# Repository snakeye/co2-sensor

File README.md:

# Carbon Dioxide Sensor MH-Z19b - ESP8266 Prototype

This project utilizes the MH-Z19b carbon dioxide sensor module, which provides a simple and cost-effective way to measure CO2 concentration via UART interface. The sensor measures concentrations in the range of 0-5000ppm, making it suitable for various environmental monitoring applications.

The device is built using the ESP12e module and features an RGB LED to indicate CO2 concentration levels.

## Features

- **CO2 concentration measurement** from 400ppm to 5000ppm using the MH-Z19b sensor.
- **RGB LED indication** with different light modes based on CO2 levels.
  
### LED Modes:

- **Steady Green Light**: CO2 concentration in the range of 400-1000ppm (normal levels).
- **Breathing Light**: Color changes from green to orange as CO2 levels increase from 1000 to 1500ppm.
- **Fast Breathing Light**: Color changes from orange to red as CO2 levels increase from 1500 to 2000ppm.
- **Fast Blinking Red Light**: CO2 concentration exceeds 2000ppm (dangerous levels).
- **Steady Blue Light**: Indicates that an OTA (Over-the-Air) update is in progress.

## Firmware

The firmware for the device is written using **PlatformIO** and the **Arduino** platform. The software controls the sensor, processes the data, and adjusts the LED indications based on the CO2 concentration.

## License

This project is licensed under the MIT License - see the [LICENSE](LICENSE) file for details.

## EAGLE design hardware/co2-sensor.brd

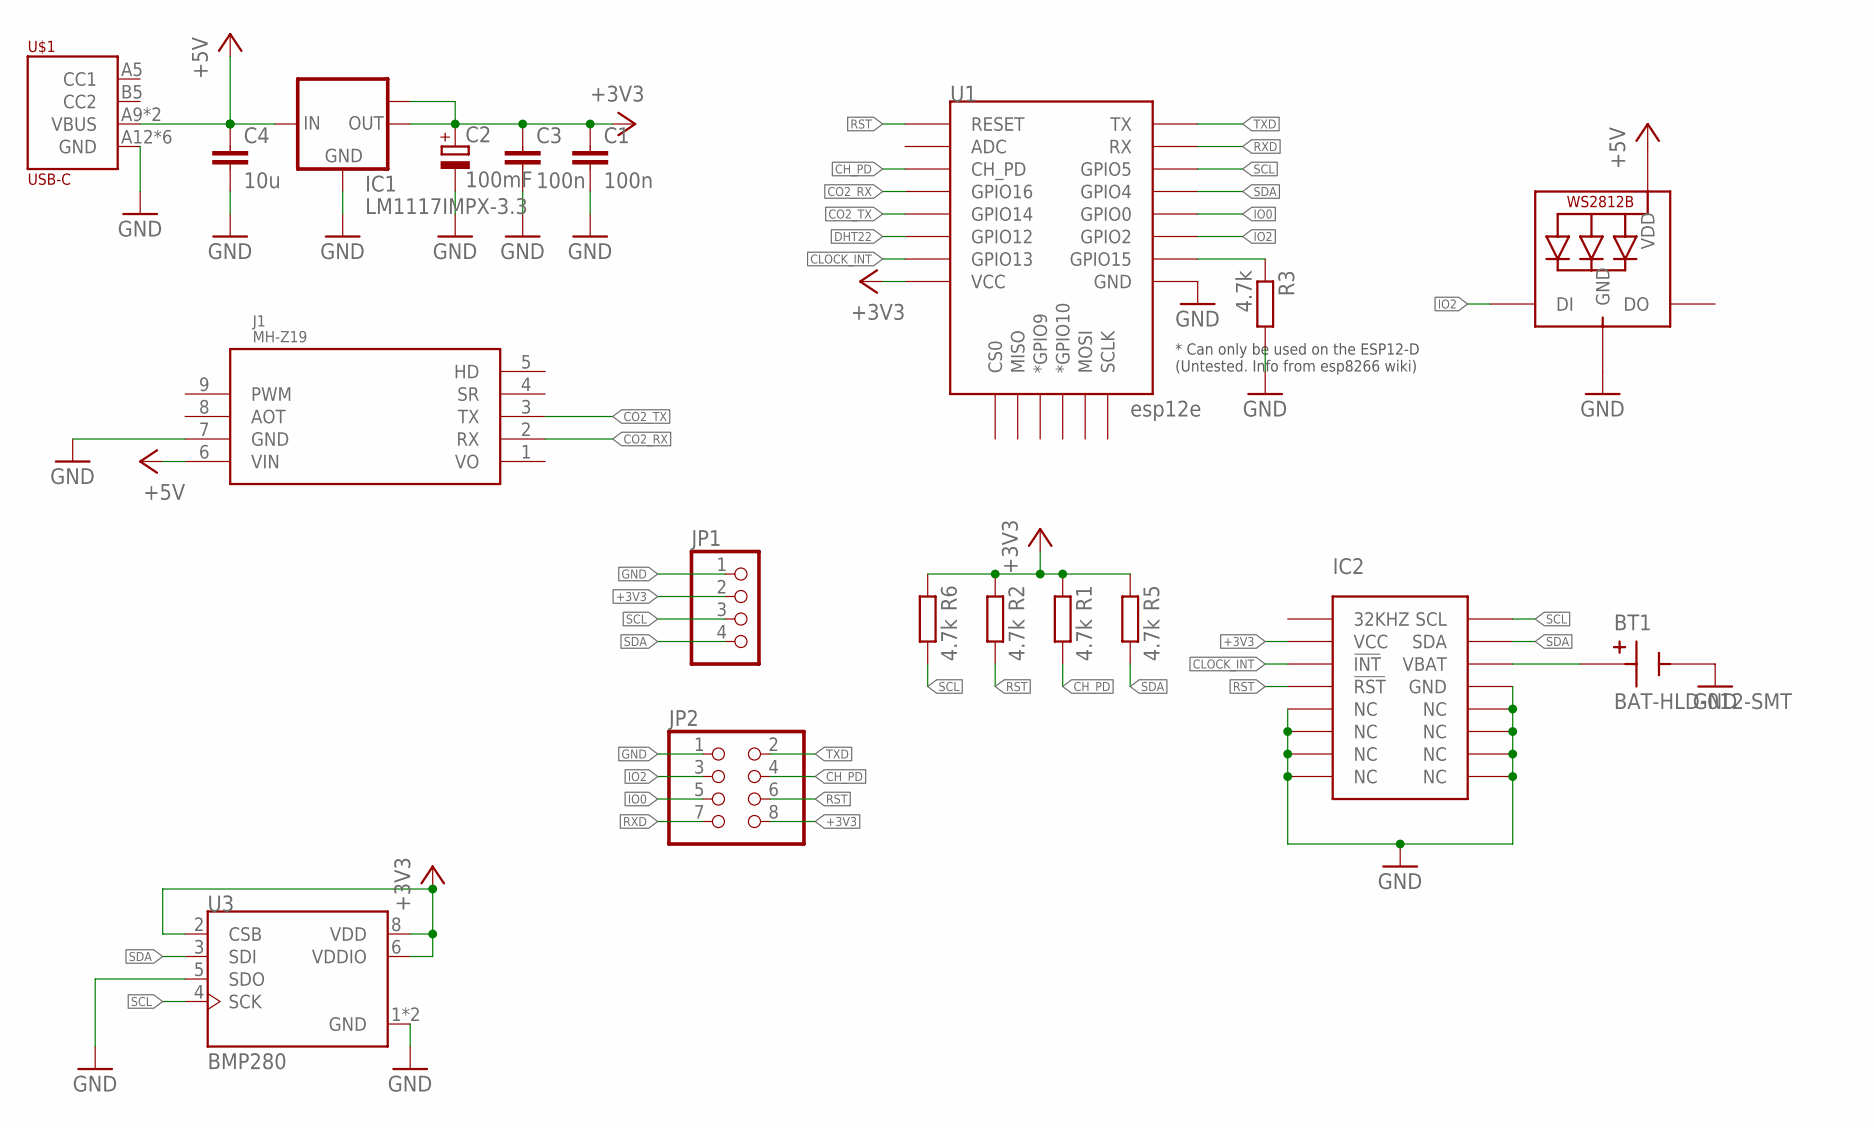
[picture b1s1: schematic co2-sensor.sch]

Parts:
BT1: BAT-HLD-012-SMT; BAT_BAT-HLD-012-SMT
C1, C3: 100n; C0805
C2: 100mF; CT3216
C4: 10u; C0805
IC1: LM1117IMPX-3.3; SOT223
IC2: DS3231SOIC-16W; SOIC-16W
J1: MH-Z19; MH-Z19-REV
JP1: PINHD-1X4; 1X04
JP2: PINHD-2X4; 2X04
LED1: WS2812B5050; WS2812B
R1, R2, R3, R5, R6: 4.7k; M0805
U1: esp12e; ESP12E-SMD
U3: BMP280; XDCR_BMP280
U$1: USB-C

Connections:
+3V3: C1.1, C2.+, C3.1, IC1.2 (OUT), IC1.TAB (OUT1), IC2.2 (VCC), JP1.2, JP2.8, R1.1, R2.1, R5.1, R6.1, U1.VCC, U3.2 (CSB), U3.6 (VDDIO), U3.8 (VDD)
+5V: C4.1, IC1.3 (IN), J1.6 (VIN), LED1.1-VDD (VDD), U$1.A9 (VBUS), U$1.B9 (VBUS)
CH_PD: JP2.4, R1.2, U1.CH_PD
CLOCK_INT: IC2.3 (!INT), U1.GPIO13
CO2_RX: J1.2 (RX), U1.GPIO16
CO2_TX: J1.3 (TX), U1.GPIO14
DHT22: U1.GPIO12
GND: BT1.N, C1.2, C2.-, C3.2, C4.2, IC1.1 (GND), IC2.5 (NC), IC2.6 (NC), IC2.7 (NC), IC2.8 (NC), IC2.9 (NC), IC2.10 (NC), IC2.11 (NC), IC2.12 (NC), IC2.13 (GND), J1.7 (GND), JP1.1, JP2.1, LED1.3-GND (GND), R3.2, U1.GND, U3.1 (GND), U3.5 (SDO), U3.7 (GND), U$1.A12 (GND), U$1.B12 (GND), U$1.P$7 (GND), U$1.P$8 (GND), U$1.P$9 (GND), U$1.P$10 (GND)
IO0: JP2.5, U1.GPIO0
IO2: JP2.3, LED1.4-DIN (DI), U1.GPIO2
unnamed: R3.1, U1.GPIO15
unnamed: BT1.P1, BT1.P2, IC2.14 (VBAT)
RST: IC2.4 (!RST), JP2.6, R2.2, U1.RESET
RXD: JP2.7, U1.RXD0 (RX)
SCL: IC2.16 (SCL), JP1.3, R6.2, U1.GPIO5, U3.4 (SCK)
SDA: IC2.15 (SDA), JP1.4, R5.2, U1.GPIO4, U3.3 (SDI)
TXD: JP2.2, U1.TXD0 (TX)
VO: J1.1 (VO)

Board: 2 copper layers, 19 parts (2 on the bottom side), 16 nets, no tracks yet.

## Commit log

2018-10-22 Eagle schematic and board
2018-11-17 fixed prototype issues
2019-04-07 platformio.ini
2019-04-08 moved to platformio
2019-04-09 indicator effects
2019-04-09 Updated blink effects
2020-04-07 Readme update
2020-11-18 ESPHome
2020-11-23 simple sketch
2023-01-26 Added schematics
2023-01-26 Working esphome config
2023-12-28 Enable Home Assistant API
2024-05-01 Expose calibration endpoint
2024-12-25 Simple version
2024-12-25 Add renovate.json
2024-12-25 Bump starlette from 0.39.2 to 0.40.0
    Bumps [starlette](https://github.com/encode/starlette) from 0.39.2 to 0.40.0.
    - [Release notes](https://github.com/encode/starlette/releases)
    - [Changelog](https://github.com/encode/starlette/blob/master/docs/release-notes.md)
    - [Commits](https://github.com/encode/starlette/compare/0.39.2...0.40.0)
    ---
    updated-dependencies:
2024-12-26 More visual modes
2025-01-03 Disabled automatic calibration; added manual calibration
2025-01-07 Simple version
    * More visual modes
    * Disable startup checks
2025-04-10 refactor, home assistant, arduino json
